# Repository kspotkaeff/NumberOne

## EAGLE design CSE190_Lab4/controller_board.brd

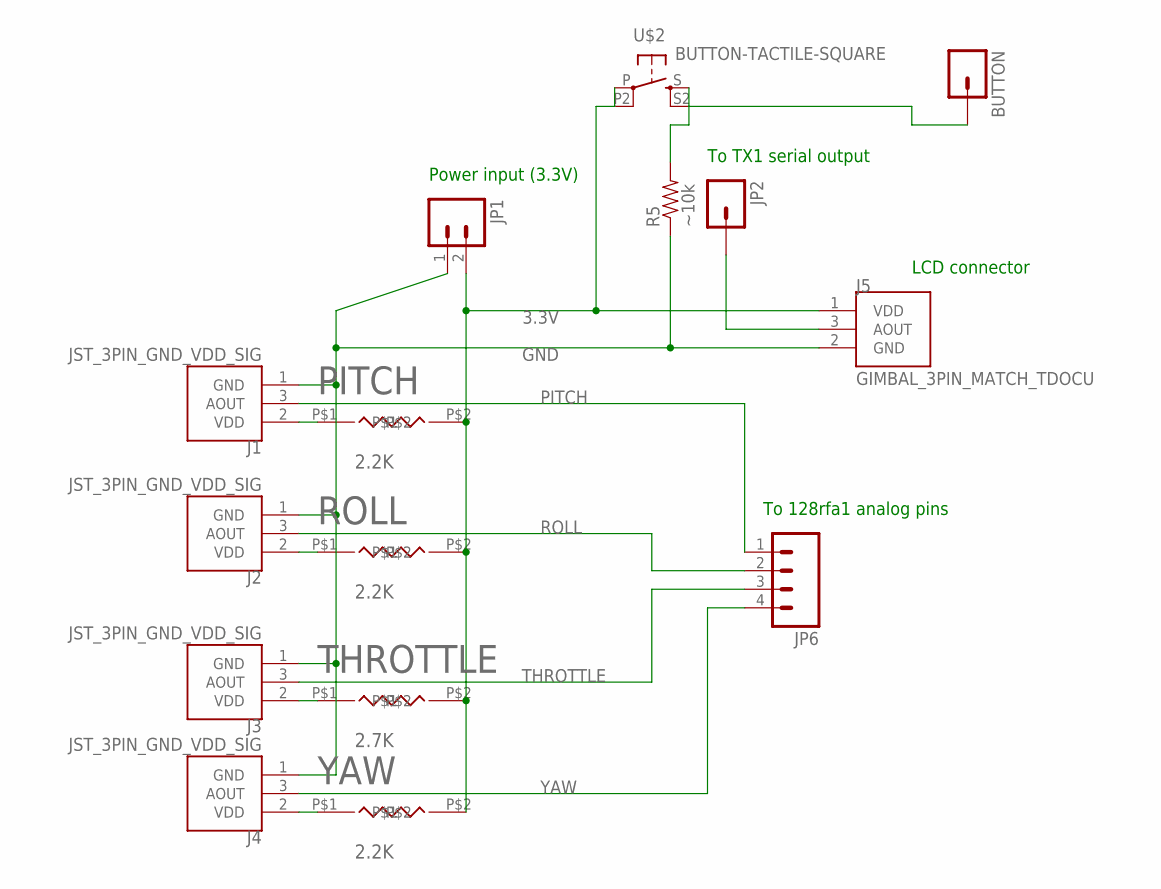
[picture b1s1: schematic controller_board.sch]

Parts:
BUTTON: M01PTH; 1X01
J1, J2, J3, J4: JST_3PIN_GND_VDD_SIG; JST-3-PTH-REVERSE
J5: GIMBAL_3PIN_MATCH_TDOCU; JST-3-PTH
JP1: M021X02_NO_SILK; 1X02_NO_SILK
JP2: M01PTH; 1X01
JP6: M04PTH; 1X04
PITCH: 2.2K; RESISTOR_THROUGH_HOLE
R5: ~10k; AXIAL-0.4
ROLL: 2.2K; RESISTOR_THROUGH_HOLE
THROTTLE: 2.7K; RESISTOR_THROUGH_HOLE
U$2: BUTTON-TACTILE-SQUARE; BUTTON-TACTILE-SQUARE-ADAFRUIT1010
YAW: 2.2K; RESISTOR_THROUGH_HOLE

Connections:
3.3V: J5.1 (VDD), JP1.2, PITCH.P$2, ROLL.P$2, THROTTLE.P$2, U$2.P, U$2.P2 (P1), YAW.P$2
GND: J1.1 (GND), J2.1 (GND), J3.1 (GND), J4.1 (GND), J5.2 (GND), JP1.1, R5.P$1 (1)
unnamed: J1.2 (VDD), PITCH.P$1
unnamed: J2.2 (VDD), ROLL.P$1
unnamed: J3.2 (VDD), THROTTLE.P$1
unnamed: J4.2 (VDD), YAW.P$1
unnamed: BUTTON.1, R5.P$2 (2), U$2.S, U$2.S2 (S1)
unnamed: J5.3 (AOUT), JP2.1
PITCH: J1.3 (AOUT), JP6.1
ROLL: J2.3 (AOUT), JP6.2
THROTTLE: J3.3 (AOUT), JP6.3
YAW: J4.3 (AOUT), JP6.4

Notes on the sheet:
To 128rfa1 analog pins
LCD connector
Power input (3.3V)
To TX1 serial output

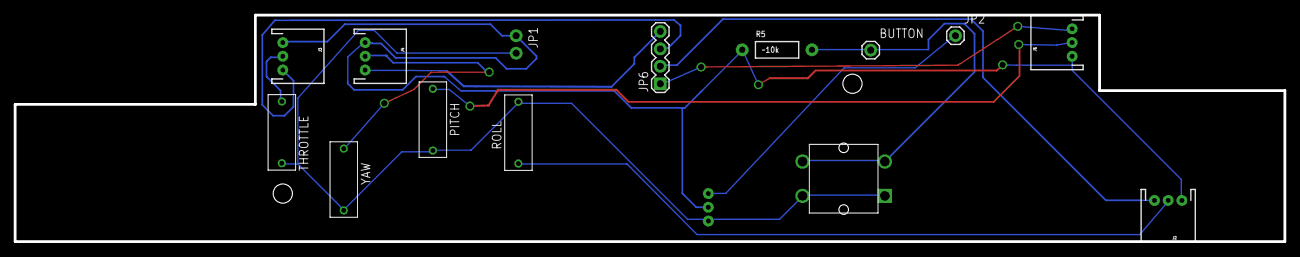
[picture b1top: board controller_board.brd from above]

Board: 2 copper layers, 185.0 x 33.0 mm, 16 parts (1 on the bottom side), 12 nets.

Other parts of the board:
U$1: CONNECTOR_BOARD_OUTLINE

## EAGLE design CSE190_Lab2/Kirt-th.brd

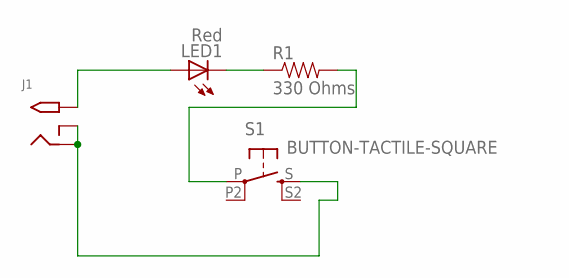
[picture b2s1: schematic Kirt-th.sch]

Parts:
J1: 2.1MMJACKTHM; PJ-102A
LED1: Red; LED5MM
R1: 330 Ohms; AXIAL-0.3
S1: BUTTON-TACTILE-SQUARE; BUTTON-TACTILE-SQUARE-ADAFRUIT1010

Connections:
unnamed: LED1.K (C), R1.P$1 (1)
unnamed: R1.P$2 (2), S1.P
unnamed: J1.TIP, LED1.A
unnamed: J1.RING, J1.RING_SW, S1.S

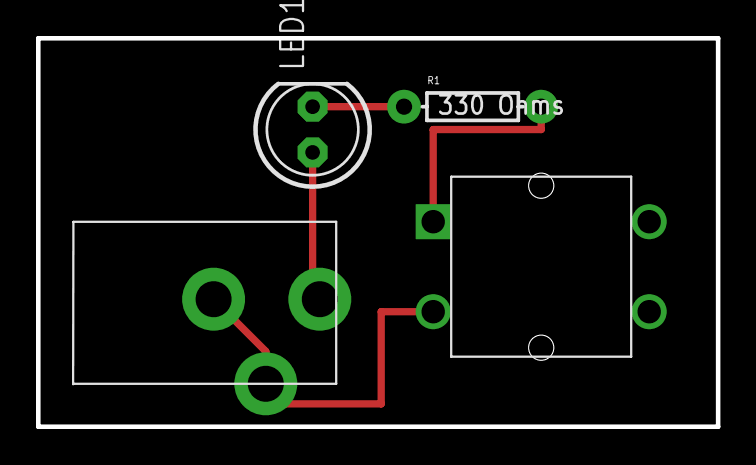
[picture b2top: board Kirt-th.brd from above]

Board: 2 copper layers, 37.8 x 21.6 mm, 4 parts (0 on the bottom side), 4 nets.

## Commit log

2015-04-07 Second Commit
2015-04-07 Third
2015-04-07 Fourth
2015-04-10 Lab 2 (uploaded for Kirt)
2015-04-17 Lab4
    LAb4 Kirt Spotkaeff A11535776

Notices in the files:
parts and their libraries:
SparkFun-Connectors: Licensing: Creative Commons ShareAlike 4.0 International - https://creativecommons.org/licenses/by-sa/4.0
